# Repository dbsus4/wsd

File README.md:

wsd
===

Rasppi python for the wsd_project, a urban portable led display

pratipo.org with iDensitat for park(ing) day @Paris + @Barcelona, September 2013

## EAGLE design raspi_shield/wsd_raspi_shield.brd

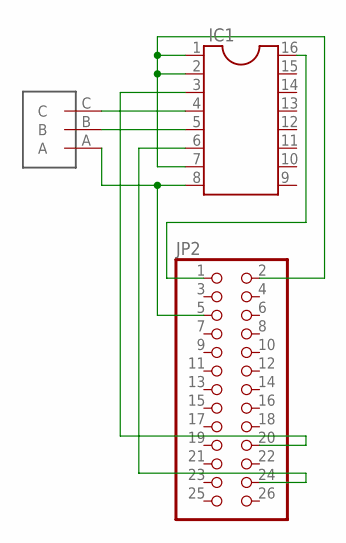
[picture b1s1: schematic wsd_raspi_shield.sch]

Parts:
IC1: DIL16
JP2: PINHD-2X13; 2X13
U$1: TERMINALBLOCK_3P_3.5MM

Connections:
unnamed: IC1.8, JP2.5, U$1.A
unnamed: IC1.16, JP2.1
unnamed: IC1.3, JP2.20
unnamed: IC1.1, IC1.2, IC1.7, JP2.2
unnamed: IC1.6, JP2.24
unnamed: IC1.5, U$1.B
unnamed: IC1.4, U$1.C

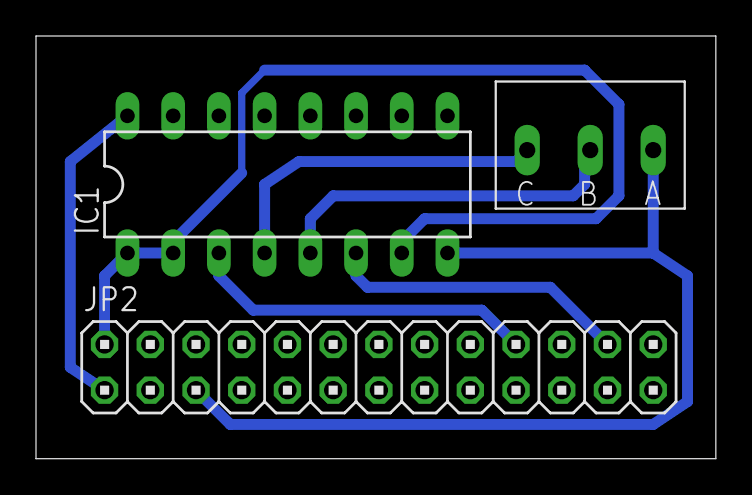
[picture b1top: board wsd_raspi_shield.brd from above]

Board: 2 copper layers, 37.8 x 23.5 mm, 3 parts (0 on the bottom side), 7 nets.

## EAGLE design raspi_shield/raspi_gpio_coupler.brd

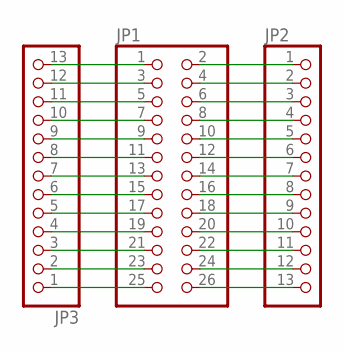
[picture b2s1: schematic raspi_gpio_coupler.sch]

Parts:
JP1: PINHD-2X13; 2X13
JP2, JP3: PINHD-1X13; 1X13

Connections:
unnamed: JP1.1, JP3.13
unnamed: JP1.3, JP3.12
unnamed: JP1.5, JP3.11
unnamed: JP1.7, JP3.10
unnamed: JP1.9, JP3.9
unnamed: JP1.11, JP3.8
unnamed: JP1.13, JP3.7
unnamed: JP1.15, JP3.6
unnamed: JP1.17, JP3.5
unnamed: JP1.19, JP3.4
unnamed: JP1.21, JP3.3
unnamed: JP1.23, JP3.2
unnamed: JP1.25, JP3.1
unnamed: JP1.2, JP2.1
unnamed: JP1.4, JP2.2
unnamed: JP1.6, JP2.3
unnamed: JP1.8, JP2.4
unnamed: JP1.10, JP2.5
unnamed: JP1.12, JP2.6
unnamed: JP1.14, JP2.7
unnamed: JP1.16, JP2.8
unnamed: JP1.18, JP2.9
unnamed: JP1.20, JP2.10
unnamed: JP1.22, JP2.11
unnamed: JP1.24, JP2.12
unnamed: JP1.26, JP2.13

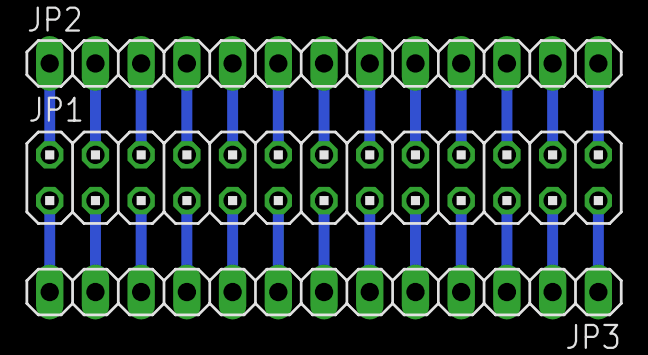
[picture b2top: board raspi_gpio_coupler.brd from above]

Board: 2 copper layers, 3 parts (0 on the bottom side), 26 nets.

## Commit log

2013-09-16 add source files
2013-09-16 testing on raspi
2013-09-16 twitter query changes
2013-09-16 gpio test file added
2013-09-16 gpio test file modified
2013-09-16 gpio test writting to spi
2013-09-16 adafruit test added
2013-09-16 tweaks on test programs
2013-09-16 modifications on bytearray vs arrays-of-bytearrays
2013-09-16 display class main features working! todo: rolling text
2013-09-17 rolling text feature added
2013-09-17 rolling text tweaks
2013-09-17 testing main
2013-09-17 testing twitter->display
2013-09-17 wsd working on raspi
2013-09-17 redone licenses
2013-09-20 adhoc changes
2013-09-20 end of commiting rush (updating raspi script through internet :$ doubled rolling speed)
2013-09-20 final tweaks
2013-09-20 hashtag string checks
2013-09-20 speed up a bit more, adjusted rolling length
2014-09-01 sntk upgrade
2014-09-01 eagle files for raspberry shield added
2014-09-17 re-structured twitter queries. new class for multi feature implementation
2014-09-17 cleaned up
2014-09-17 multi url removal + skipping url-less bodies
2015-04-22 opendors @hangar
2015-04-22 v4 #TerritoriGuiri @santamonica
2015-04-22 gitignore change
2015-04-22 finnishing tweaks
2015-07-09 territoriguiri july update
2015-09-25 september 2015
